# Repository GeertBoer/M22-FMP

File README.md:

# Repository for Soundit and Ecouter Exercises
 
Code and designs by Geert Boer, Coached by prof.dr.ir. J.H. (Berry) Eggen.
Project for Industial Design Master graduation at Eindhoven University of Technology. 

Use Soundit3 code folder.

Soundit is possible in part thanks to the efforts of Paul Stoffregen https://www.pjrc.com/store/teensy40.html

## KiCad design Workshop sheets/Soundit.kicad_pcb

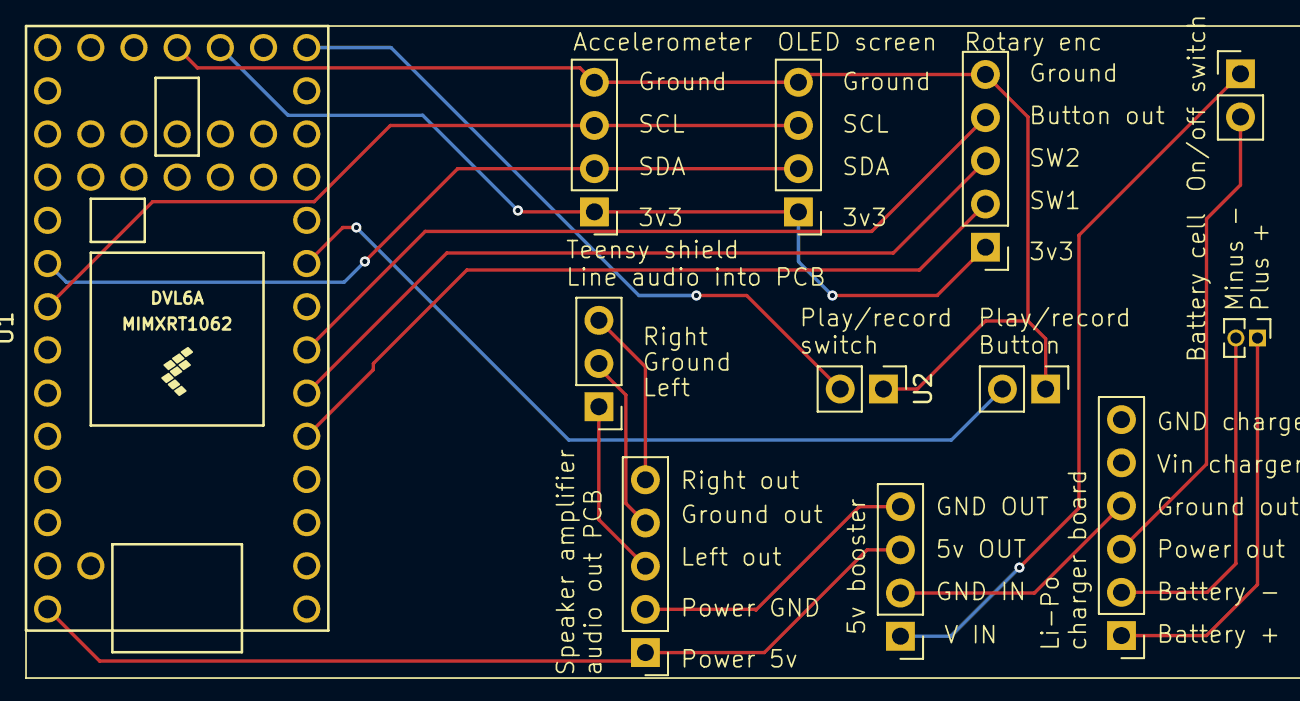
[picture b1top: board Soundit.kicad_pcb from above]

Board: 2 copper layers, 12 parts (0 on the bottom side), 19 nets.

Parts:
5v_booster1: PinHeader_1x04_P2.54mm_Vertical
Accel1: PinHeader_1x04_P2.54mm_Vertical
AudioLine1: PinHeader_1x03_P2.54mm_Vertical
BT1: Battery_Cell; PinHeader_1x02_P1.27mm_Vertical
Charger1: PinHeader_1x06_P2.54mm_Vertical
OLED1: PinHeader_1x04_P2.54mm_Vertical
ON/OFF_SW1: onoff_sw; PinHeader_1x02_P2.54mm_Vertical
Record_btn1: rec_btn; PinHeader_1x02_P2.54mm_Vertical
Rotary1: PinHeader_1x05_P2.54mm_Vertical
Speakeramp1: PinHeader_1x05_P2.54mm_Vertical
U1: Teensy4.0; Teensy40
U2: PinHeader_1x02_P2.54mm_Vertical

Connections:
unnamed: 5v_booster1.3 (5V_out), Speakeramp1.1 (5V), U1.33 (VIN)
unnamed: 5v_booster1.2 (GND_in), Charger1.4 (GNDout)
unnamed: 5v_booster1.4 (GND_out), Speakeramp1.2 (GND), U1.32 (GND)
unnamed: 5v_booster1.1 (V_in), ON/OFF_SW1.1 (A)
unnamed: Accel1.1 (3V3), OLED1.1 (3v3), Rotary1.1 (Vin), U1.16 (3V3)
unnamed: Accel1.4 (GND), OLED1.4 (GND), Record_btn1.1, Rotary1.5 (GND), U1.17 (GND), U2.1 (A)
unnamed: Accel1.3 (SCL), OLED1.3 (SCL), U1.26 (19_A5_SCL0)
unnamed: Accel1.2 (SDA), OLED1.2 (SDA), U1.25 (18_A4_SDA0)
unnamed: AudioLine1.2 (Ground), Speakeramp1.4 (GND-LR)
unnamed: AudioLine1.1 (Left), Speakeramp1.3 (L-IN)
unnamed: AudioLine1.3 (Right), Speakeramp1.5 (R-IN)
unnamed: BT1.1 (+), Charger1.1 (Vbat)
unnamed: BT1.2 (-), Charger1.2 (GNDbat)
unnamed: Charger1.3 (Vout), ON/OFF_SW1.2 (B)
unnamed: Rotary1.4 (BTN), U1.7 (5_IN2)
unnamed: Rotary1.2 (SW1), U1.5 (3_LRCLK2)
unnamed: Rotary1.3 (SW2), U1.6 (4_BCLK2)
unnamed: Record_btn1.2, U1.9 (7_RX2_OUT1A)
unnamed: U1.14 (12_MISO_MQSL), U2.2 (B)

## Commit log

2024-05-15 Initial commit, lots of UI work
2024-05-15 Ram veel features erin zo goed als klaar
2024-05-15 from byte to uint to avoid compiler errors for newer teensys
2024-05-15 UI improvements
2024-05-16 Change gain on mic
2024-05-16 Adding submenus..
2024-05-16 In the process of adding submenus to playback mode
2024-05-16 Submenu implemented.
2024-05-16 Remove some lines and comments
2024-05-16 delay implemented
2024-05-16 Demoable version
2024-05-16 Working on fx changing implementation, big part of UX is there but audio system is not finished or handled
2024-05-16 Set to recorder mode
2024-05-22 Progress on FX selector.
    What has to happen is: memory/save after power off, and maybe per sample memory.
    Also check if certain combinations don't break FX chain.
2024-05-23 Soundit now remembers last FX
2024-05-23 Fixed bug where reverse was not remembered
2024-05-23 reset fx when device is flat
2024-05-23 Finetuned reverse fx and added fx thresh for sensor
2024-05-27 Changed volume changer logic UI drawing for an experiment
    It was just bashing the screen with updates causing it to tear (I h8 tearing)
2024-05-27 Added some comments and cleanups
2024-05-31 Soundit 3 made for new case
2024-06-05 Some UI changes: Demo day ready :))
2024-06-11 Changed some volume settings
2024-06-11 Uploaded PCB files
2024-06-11 Uploaded sheets and changed some folder names
2024-08-07 added accelerometer test code
